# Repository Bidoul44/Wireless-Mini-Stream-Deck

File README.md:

# Wireless Mini Stream Deck

A compact wireless macro pad designed and built during Hack Club's Half-Life / PCB Week.

## Project

The goal of this project is to create a small and reusable wireless controller for a computer.

The device will feature:

* 6 programmable buttons
* 3 analog potentiometers
* Bluetooth connectivity
* ESP32-S3 microcontroller
* Rechargeable LiPo battery
* USB-C charging
* Physical power switch
* Status LED
* Custom 2-layer PCB
* Custom 3D-printed enclosure

The ESP32-S3 will be mounted as a removable module so it can be reprogrammed and reused in future projects.

## How it works

The ESP32-S3 reads the six physical buttons and the three potentiometers.

The buttons can be assigned to custom keyboard shortcuts or macros, while the potentiometers can be used as analog controls.

The ESP32-S3 communicates wirelessly with the computer using Bluetooth.

The PCB integrates the controls, power system, battery connection, USB-C charging and the ESP32-S3 module.

## Hardware

The PCB is designed as a compact 2-layer board.

Main components:

* ESP32-S3 module
* 6 tactile push buttons
* 3 × 10 kΩ potentiometers
* LiPo battery
* USB-C charging circuit
* Power switch
* Status LED
* Supporting resistors and capacitors

## Firmware

The firmware is written for the ESP32-S3.

It will handle:

* Button inputs
* Potentiometer readings
* Bluetooth communication
* Custom macros
* Power management

The firmware is designed to remain reprogrammable so the functions of the controls can be changed later.

## PCB Design

The PCB and schematic are designed using KiCad.

### 3D Preview

### Schematic

## Project Status

* [x] Project concept
* [x] Component architecture
* [x] Schematic
* [x] PCB layout
* [x] PCB routing
* [x] Electrical checks
* [x] Manufacturing files
* [ ] PCB manufacturing
* [ ] Assembly
* [ ] Firmware
* [ ] Testing
* [ ] 3D printed enclosure

# Some photos :

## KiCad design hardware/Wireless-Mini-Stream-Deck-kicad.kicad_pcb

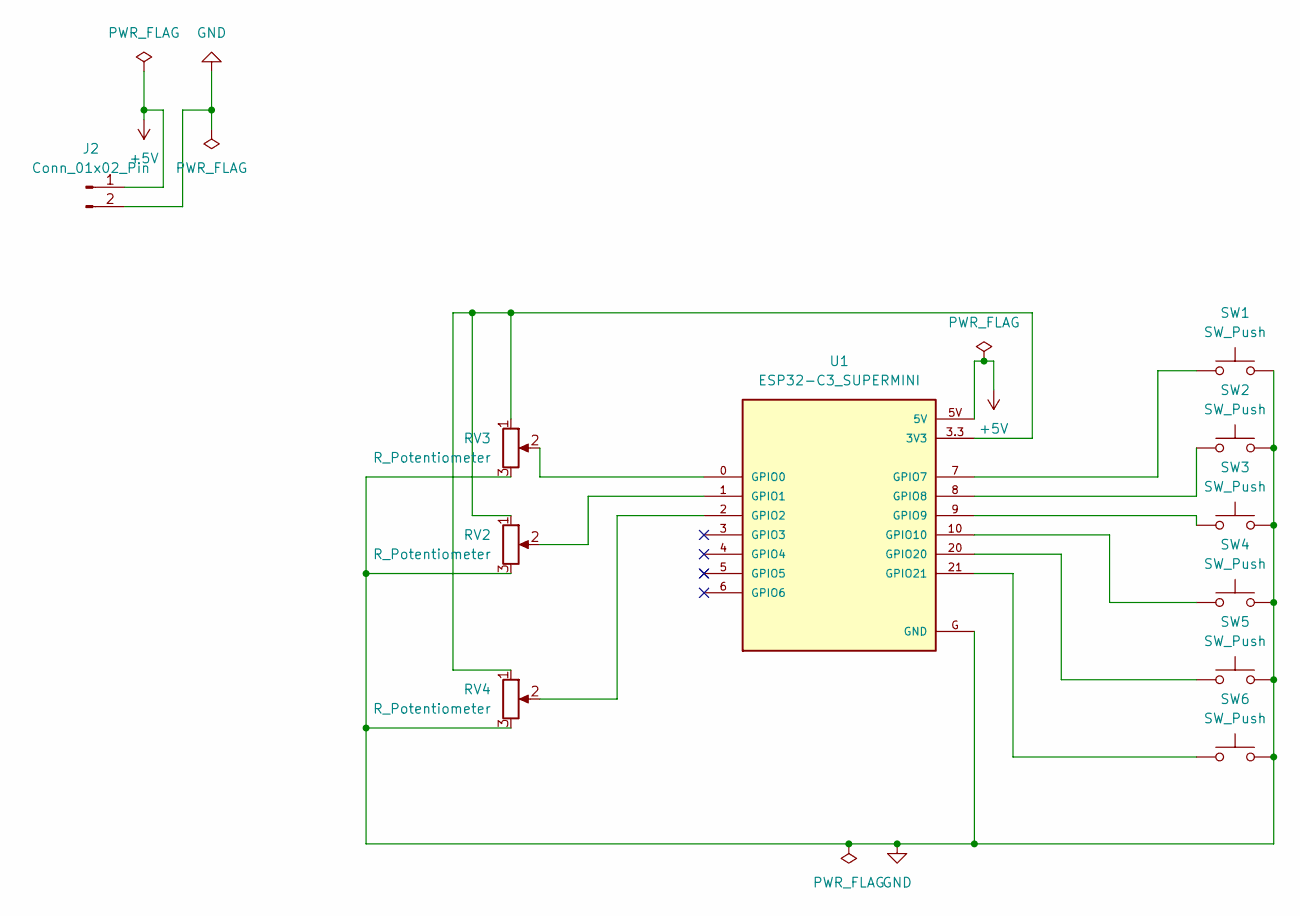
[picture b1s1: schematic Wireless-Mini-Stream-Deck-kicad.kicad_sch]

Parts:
J2: Conn_01x02_Pin; JWT_A3963_1x02_P3.96mm_Vertical
RV2, RV3, RV4: R_Potentiometer; POTENTIOMETER_BOARDMNT
SW1, SW2, SW3, SW4, SW5, SW6: SW_Push; SW_PUSH-12mm
U1: ESP32-C3_SUPERMINI; MODULE_ESP32-C3_SUPERMINI

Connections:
+5V: J2.1, U1.5V
GND: J2.2, RV2.3, RV3.3, RV4.3, SW1.2, SW2.2, SW3.2, SW4.2, SW5.2, SW6.2, U1.G (GND)
unnamed: RV2.1, RV3.1, RV4.1, U1.3.3 (3V3)
unnamed: RV3.2, U1.0 (GPIO0)
unnamed: RV2.2, U1.1 (GPIO1)
unnamed: RV4.2, U1.2 (GPIO2)
unnamed: SW1.1, U1.7 (GPIO7)
unnamed: SW2.1, U1.8 (GPIO8)
unnamed: SW3.1, U1.9 (GPIO9)
unnamed: SW4.1, U1.10 (GPIO10)
unnamed: SW5.1, U1.20 (GPIO20)
unnamed: SW6.1, U1.21 (GPIO21)

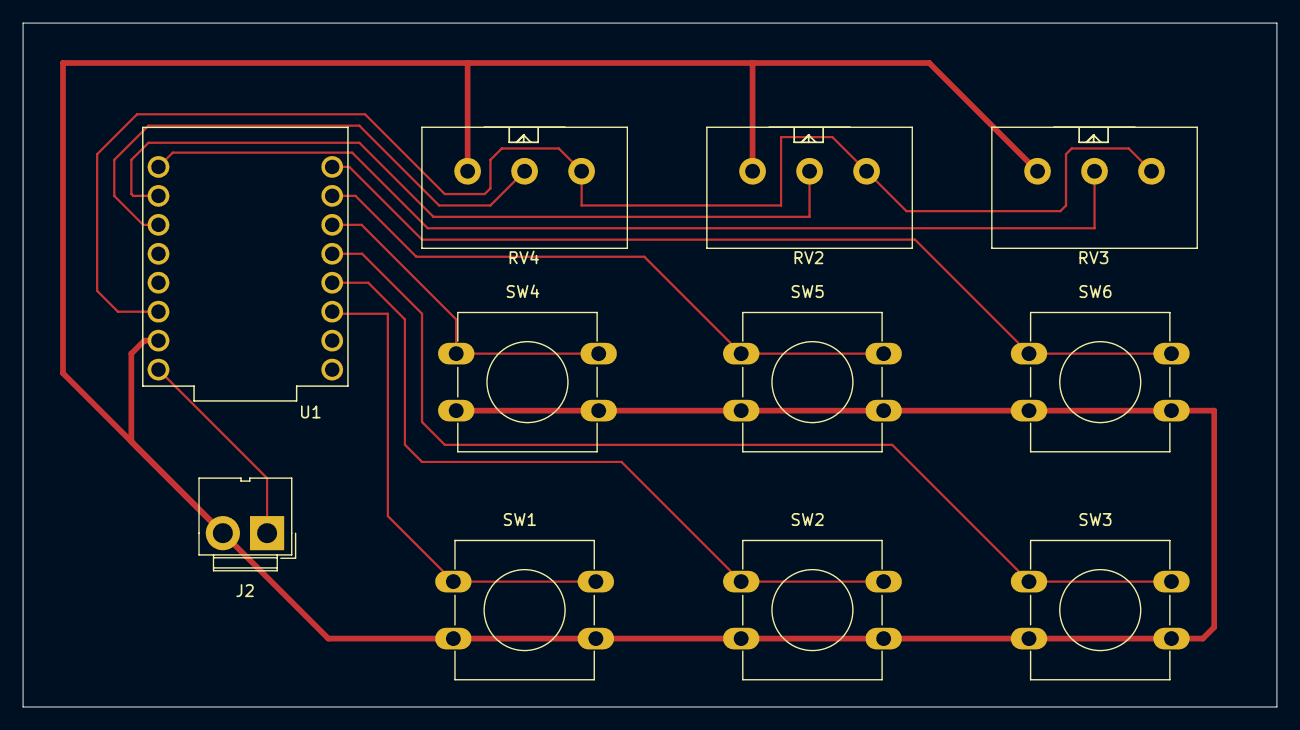
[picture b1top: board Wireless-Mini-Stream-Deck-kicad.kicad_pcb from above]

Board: 2 copper layers, 110.0 x 60.0 mm, 11 parts (0 on the bottom side), 12 nets.
